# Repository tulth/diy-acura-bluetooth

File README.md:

# diy-acura-bluetooth
Overview
====================
My DIY project to understand, communicate, and add bluetooth with a 1999 Acura RL bose head unit

Cloning
====================
Be sure to include 

    --recursive 
  
during the git clone to get the submodules!

If you missed this, and do not want to reclone, do the following:

    git submodule update --init --recursive

Building
====================
Build platform:
Arch linux 
with community package: arm-none-eabi-gcc 5.3.0-1
with community package: arm-none-eabi-newlib
with package: python

Desktop shared library
------------
    cd target_desktop
    ./make.sh

Teensy3 embedded executables
------------
    cd target_teensy3
    ./make.sh

Loading
====================
To load you will need this arch linux AUR: teensy-loader-cli

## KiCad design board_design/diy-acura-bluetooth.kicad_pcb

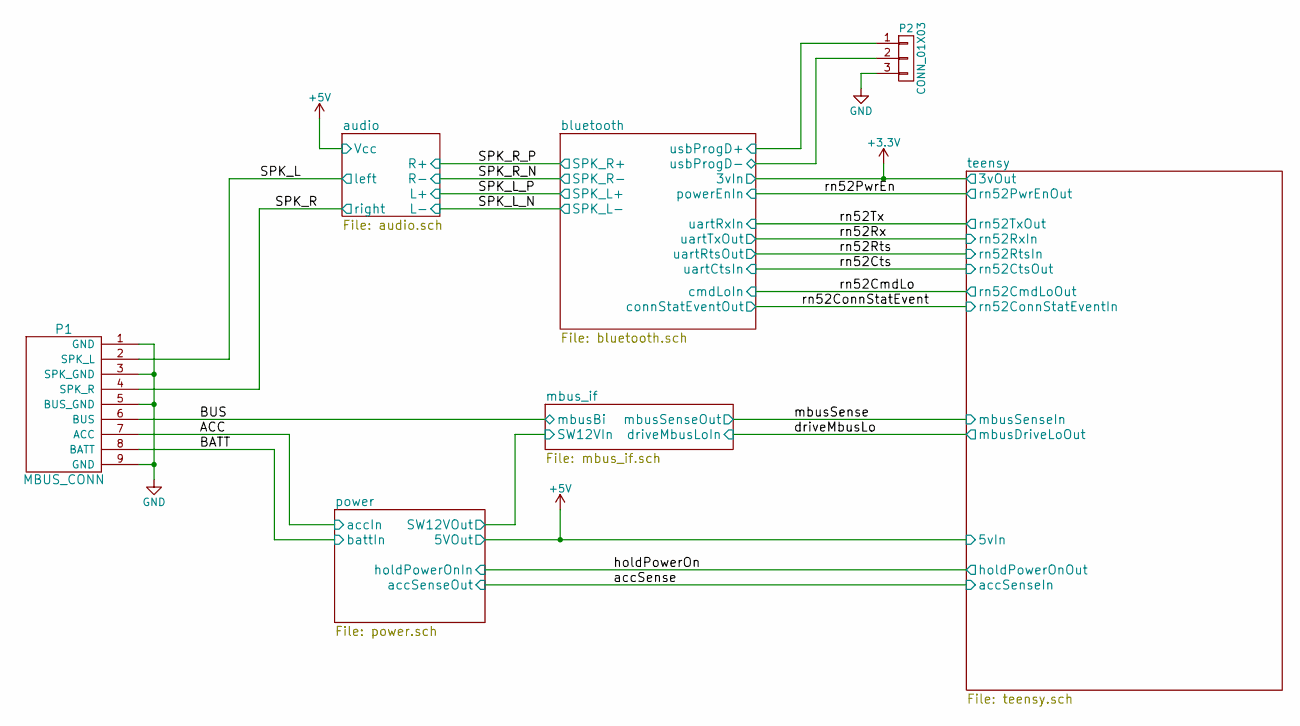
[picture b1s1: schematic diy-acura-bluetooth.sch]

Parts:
P1: MBUS_CONN; mbus_conn
P2: CONN_01X03; Pin_Header_Straight_1x03

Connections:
/audio/left: P1.2 (SPK_L); also elsewhere on the board
/audio/right: P1.4 (SPK_R); also elsewhere on the board
/bluetooth/usbProgD+: P2.1; also elsewhere on the board
/bluetooth/usbProgD-: P2.2; also elsewhere on the board
/mbus_if/mbusBi: P1.6 (BUS); also elsewhere on the board
/power/accIn: P1.7 (ACC); also elsewhere on the board
/power/battIn: P1.8 (BATT); also elsewhere on the board
GND: P1.1 (GND), P1.3 (SPK_GND), P1.5 (BUS_GND), P1.9 (GND), P2.3; also elsewhere on the board

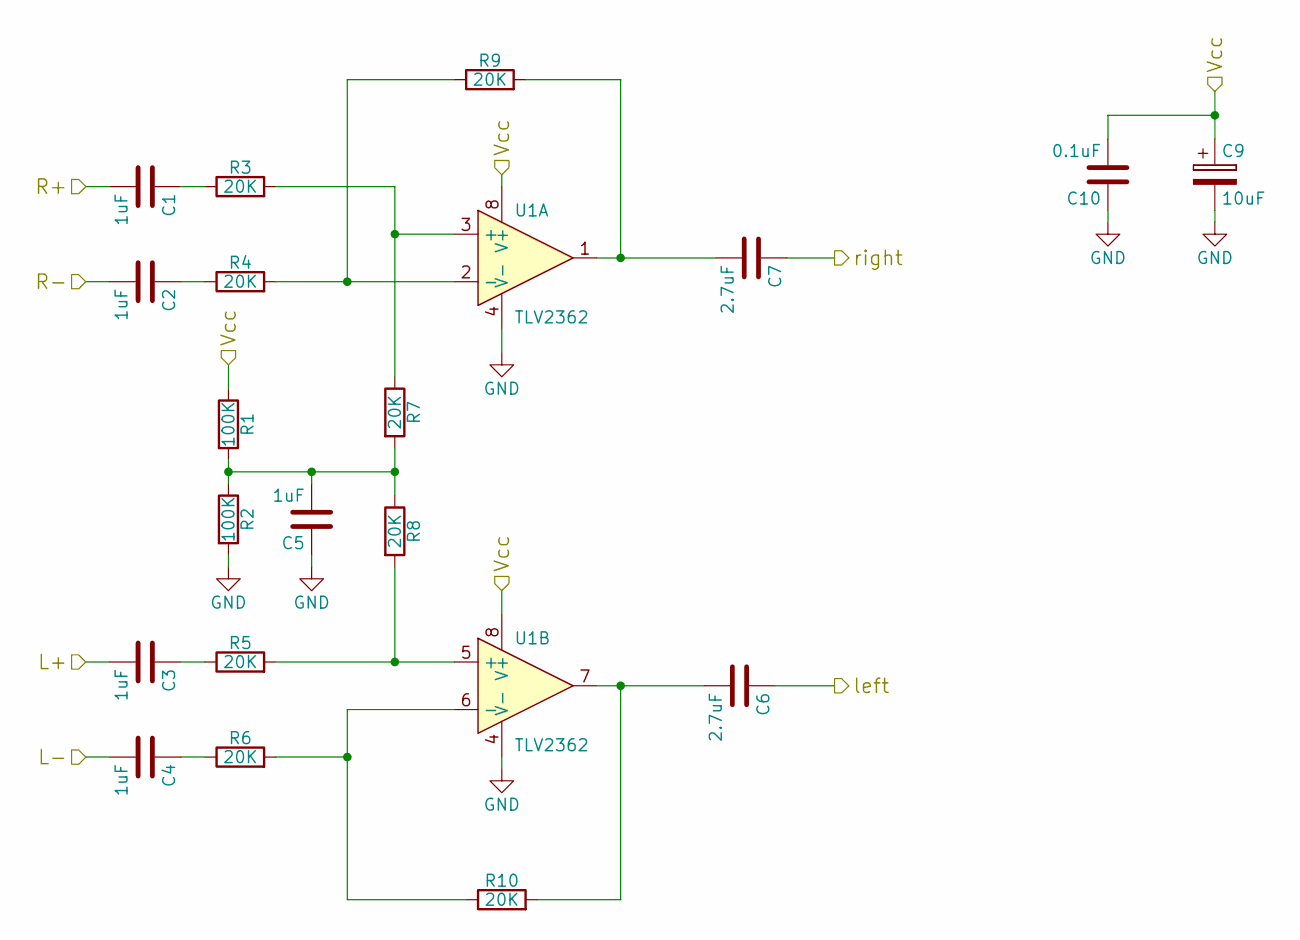
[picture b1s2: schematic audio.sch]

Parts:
C1, C2, C3, C4, C5: 1uF; C_Rect_L7.5_W6.5_P5
C6, C7: 2.7uF; C_Rect_L27_W9_H17_P23
C9: 10uF; C_Radial_D5_L11_P2
C10: 0.1uF; C_Disc_D6_P5
R1, R2: 100K; Resistor_Horizontal_RM10mm
R3, R4, R5, R6, R7, R8, R9, R10: 20K; Resistor_Horizontal_RM10mm
U1: TLV2362; DIP-8_W7.62mm_LongPads

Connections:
+5V: C9.1, C10.2, R1.1, U1.8 (V+); also elsewhere on the board
/audio/L+: C3.2; also elsewhere on the board
/audio/L-: C4.2; also elsewhere on the board
/audio/R+: C1.2; also elsewhere on the board
/audio/R-: C2.2; also elsewhere on the board
/audio/left: C6.1; also elsewhere on the board
/audio/right: C7.1; also elsewhere on the board
GND: C5.1, C9.2, C10.1, R2.2, U1.4 (V-); also elsewhere on the board
unnamed: C1.1, R3.1
unnamed: C2.1, R4.1
unnamed: C3.1, R5.1
unnamed: C4.1, R6.1
unnamed: C5.2, R1.2, R2.1, R7.2, R8.1
unnamed: C6.2, R10.2, U1.7
unnamed: C7.2, R9.2, U1.1
unnamed: R3.2, R7.1, U1.3 (+)
unnamed: R4.2, R9.1, U1.2 (-)
unnamed: R5.2, R8.2, U1.5 (+)
unnamed: R6.2, R10.1, U1.6 (-)

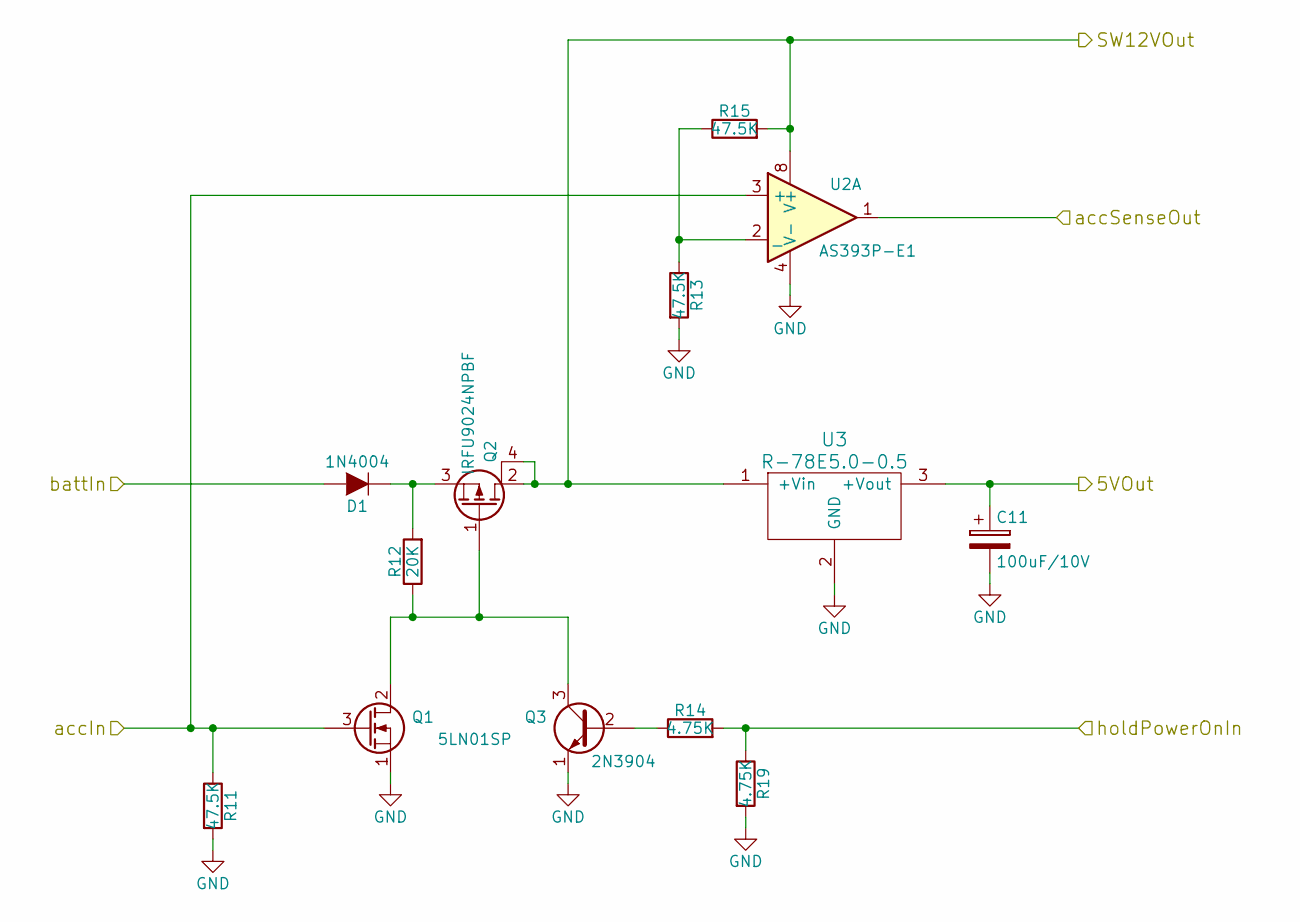
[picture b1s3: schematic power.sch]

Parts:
C11: 100uF/10V; C_Radial_D5_L11_P2
D1: 1N4004; Diode_DO-41_SOD81_Horizontal_RM10
Q1: 5LN01SP; TO-92_Molded_Wide_Oval
Q2: IRFU9024NPBF; TO-251AA-TPAD
Q3: 2N3904; TO-92_Molded_Wide_Oval
R11, R13, R15: 47.5K; Resistor_Horizontal_RM10mm
R12: 20K; Resistor_Horizontal_RM10mm
R14, R19: 4.75K; Resistor_Horizontal_RM10mm
U2: AS393P-E1; DIP-8_W7.62mm_LongPads
U3: R-78E5.0-0.5

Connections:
+5V: C11.1, U3.3 (+Vout); also elsewhere on the board
/mbus_if/SW12VIn: Q2.2 (D), Q2.4 (D), R15.2, U2.8 (V+), U3.1 (+Vin); also elsewhere on the board
/power/accIn: Q1.3 (G), R11.1, U2.3 (+); also elsewhere on the board
/power/battIn: D1.2 (A); also elsewhere on the board
/power/holdPowerOnIn: R14.2, R19.1; also elsewhere on the board
/teensy/accSenseIn: U2.1; also elsewhere on the board
GND: C11.2, Q1.1 (S), Q3.1 (E), R11.2, R13.2, R19.2, U2.4 (V-), U3.2 (GND); also elsewhere on the board
unnamed: D1.1 (K), Q2.3 (S), R12.2
unnamed: Q1.2 (D), Q2.1 (G), Q3.3 (C), R12.1
unnamed: Q3.2 (B), R14.1
unnamed: R13.1, R15.1, U2.2 (_)

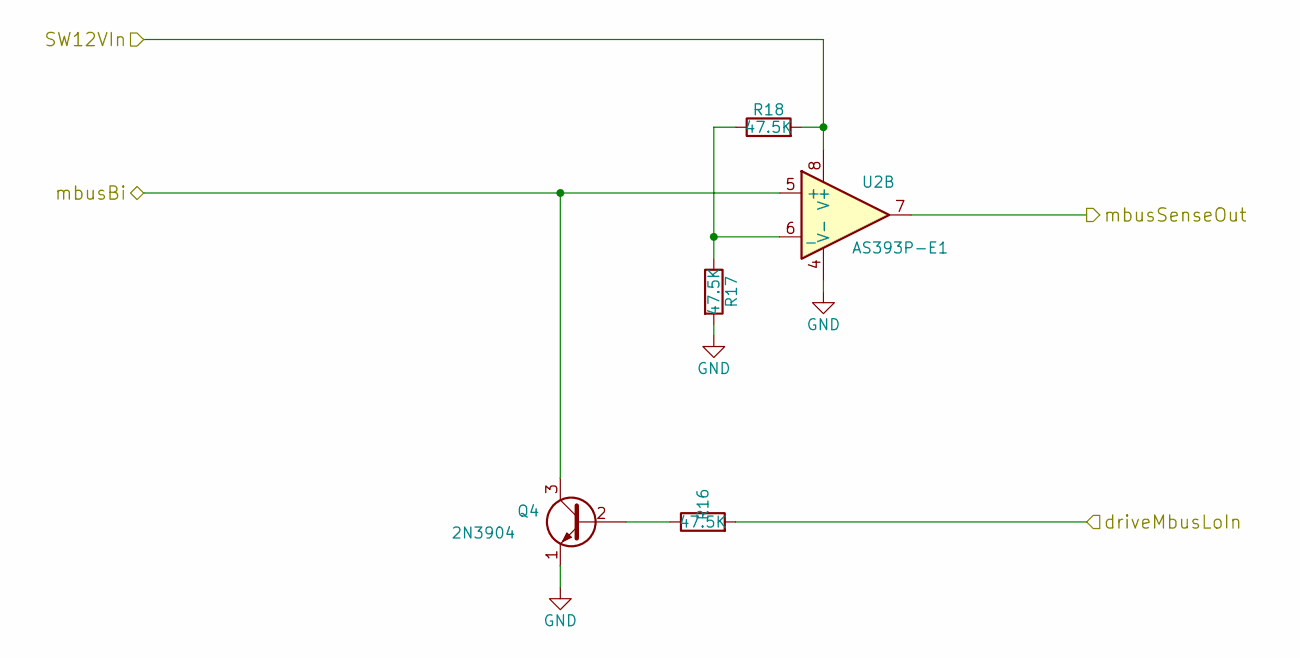
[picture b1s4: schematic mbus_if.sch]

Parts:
Q4: 2N3904; TO-92_Molded_Wide_Oval
R16, R17, R18: 47.5K; Resistor_Horizontal_RM10mm
U2: AS393P-E1; DIP-8_W7.62mm_LongPads

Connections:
/mbus_if/SW12VIn: R18.2, U2.8 (V+); also elsewhere on the board
/mbus_if/driveMbusLoIn: R16.2; also elsewhere on the board
/mbus_if/mbusBi: Q4.3 (C), U2.5 (+); also elsewhere on the board
/teensy/mbusSenseIn: U2.7; also elsewhere on the board
GND: Q4.1 (E), R17.2, U2.4 (V-); also elsewhere on the board
unnamed: Q4.2 (B), R16.1
unnamed: R17.1, R18.1, U2.6 (_)

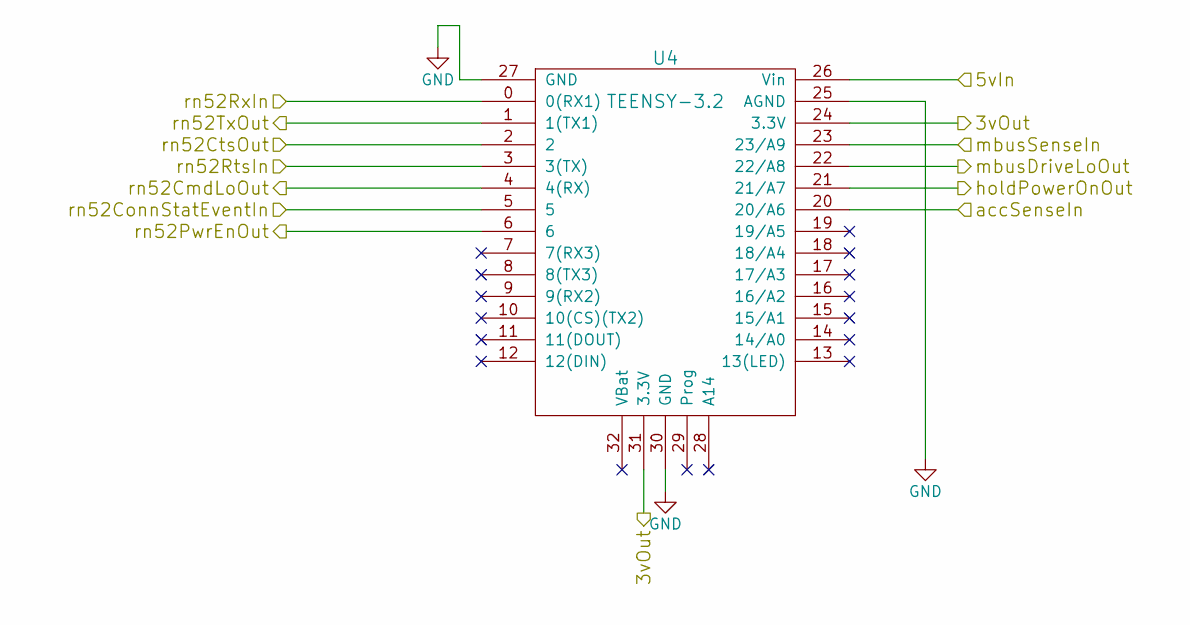
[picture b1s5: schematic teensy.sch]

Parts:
U4: TEENSY-3.2; Teensy-3.1

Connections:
+3V3: U4.24 (3.3V), U4.31 (3.3V); also elsewhere on the board
+5V: U4.26 (Vin); also elsewhere on the board
/bluetooth/cmdLoIn: U4.4 (4(RX)); also elsewhere on the board
/bluetooth/connStatEventOut: U4.5; also elsewhere on the board
/bluetooth/powerEnIn: U4.6; also elsewhere on the board
/mbus_if/driveMbusLoIn: U4.22 (22/A8); also elsewhere on the board
/power/holdPowerOnIn: U4.21 (21/A7); also elsewhere on the board
/teensy/accSenseIn: U4.20 (20/A6); also elsewhere on the board
/teensy/mbusSenseIn: U4.23 (23/A9); also elsewhere on the board
/teensy/rn52CtsOut: U4.2; also elsewhere on the board
/teensy/rn52RtsIn: U4.3 (3(TX)); also elsewhere on the board
/teensy/rn52RxIn: U4.0 (0(RX1)); also elsewhere on the board
/teensy/rn52TxOut: U4.1 (1(TX1)); also elsewhere on the board
GND: U4.25 (AGND), U4.27 (GND), U4.30 (GND); also elsewhere on the board

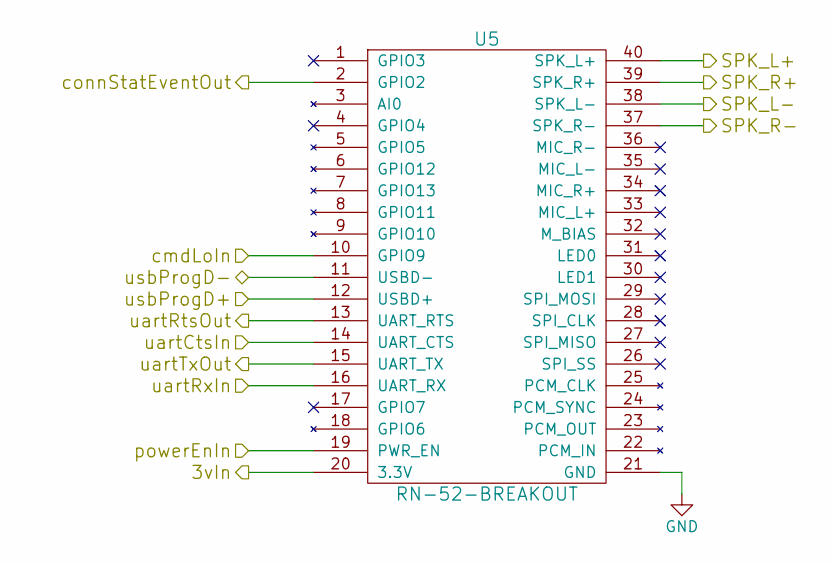
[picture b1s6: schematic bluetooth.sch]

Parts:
U5: RN-52-BREAKOUT

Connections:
+3V3: U5.20 (3.3V); also elsewhere on the board
/audio/L+: U5.40 (SPK_L+); also elsewhere on the board
/audio/L-: U5.38 (SPK_L-); also elsewhere on the board
/audio/R+: U5.39 (SPK_R+); also elsewhere on the board
/audio/R-: U5.37 (SPK_R-); also elsewhere on the board
/bluetooth/cmdLoIn: U5.10 (GPIO9); also elsewhere on the board
/bluetooth/connStatEventOut: U5.2 (GPIO2); also elsewhere on the board
/bluetooth/powerEnIn: U5.19 (PWR_EN); also elsewhere on the board
/bluetooth/usbProgD+: U5.12 (USBD+); also elsewhere on the board
/bluetooth/usbProgD-: U5.11 (USBD-); also elsewhere on the board
/teensy/rn52CtsOut: U5.14 (UART_CTS); also elsewhere on the board
/teensy/rn52RtsIn: U5.13 (UART_RTS); also elsewhere on the board
/teensy/rn52RxIn: U5.15 (UART_TX); also elsewhere on the board
/teensy/rn52TxOut: U5.16 (UART_RX); also elsewhere on the board
GND: U5.21 (GND); also elsewhere on the board

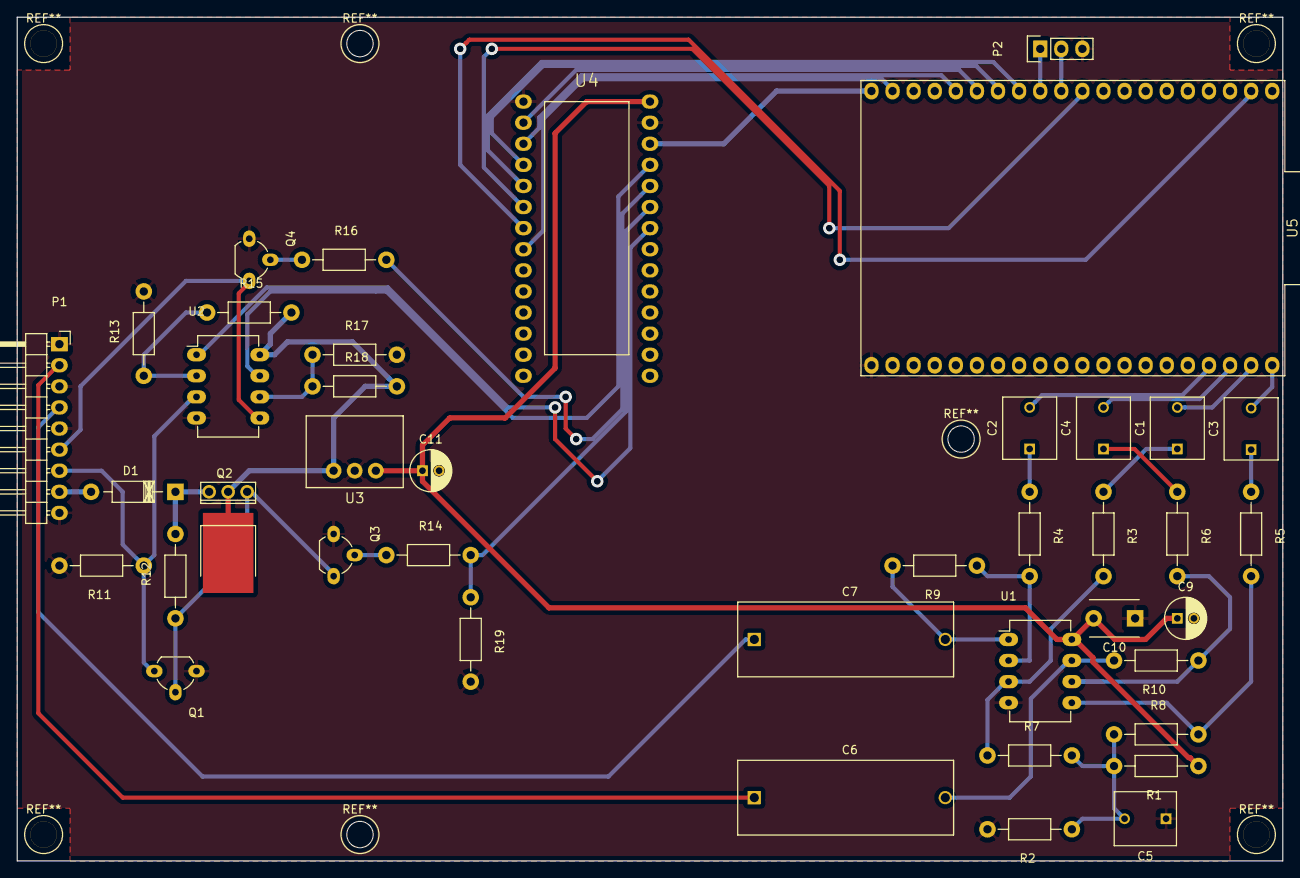
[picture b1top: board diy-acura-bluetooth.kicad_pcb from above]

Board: 2 copper layers, 152.4 x 101.6 mm, 41 parts (0 on the bottom side), 43 nets.

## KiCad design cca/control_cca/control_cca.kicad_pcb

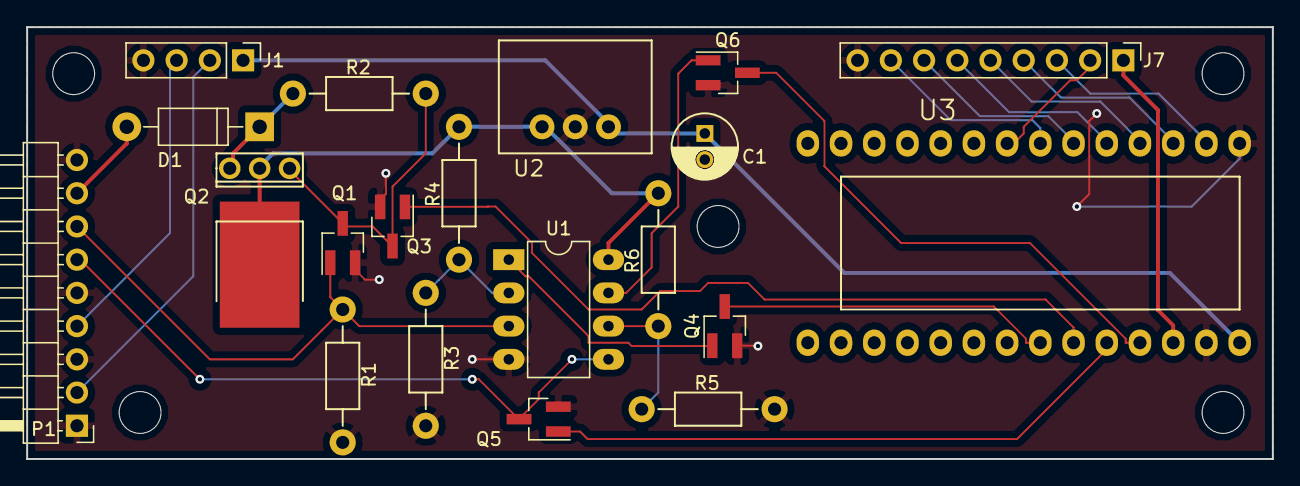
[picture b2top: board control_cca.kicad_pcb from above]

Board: 2 copper layers, 95.2 x 33.0 mm, 25 parts (0 on the bottom side), 26 nets.

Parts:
C1: ECA-1AM101; C_Radial_D5_L12_P2
D1: 1N4004; D_DO-41_SOD81_P10.16mm_Horizontal
J1: Conn_01x04; Pin_Header_Straight_1x04_Pitch2.54mm
J7: Conn_01x09; Pin_Header_Straight_1x09_Pitch2.54mm
MK1, MK2, MK3, MK4, MK5: Mounting_Hole; MountingHole_3.2mm_M3_ISO14580
P1: MBUS_CONN; Pin_Header_Angled_1x09_Pitch2.54mm
Q1, Q3, Q4, Q5, Q6: BSS138N; SOT-23_Handsoldering
Q2: IRFU9024NPBF; TO-251AA-TPAD
R1, R3, R4, R6: 47.5K; Resistor_Horizontal_RM10mm
R2, R5: 20K; Resistor_Horizontal_RM10mm
U1: AS393P-E1; DIP-8_W7.62mm_LongPads
U2: R-78E5.0-0.5
U3: TEENSY-LC; Teensy-3.2

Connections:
+3V3: J7.1, U3.24
+5V: C1.1, J1.1, U2.3, U3.26
/ACC: P1.7, Q1.1, R1.1, U1.3
/BATT: D1.2, P1.8
/BUS: P1.6, Q5.3, U1.5
/SPK_L: J1.2, P1.2
/SPK_R: J1.3, P1.4
/mbus_if/mbusDriveLowIn: Q5.1, U3.22
/power/holdPowerOnIn: Q3.1, U3.21
/power/protBattIn: D1.1, Q2.3, R2.1
/power/sw12VOut: Q2.2, Q2.4, R4.2, R6.2, U1.8, U2.1
/teensy/accLowIn: Q4.3, U3.20
/teensy/mbusSenseLowIn: Q6.3, U3.23
/teensy/rn52CmdLoOut: J7.7, U3.4
/teensy/rn52ConnStatEventIn: J7.8, U3.5
/teensy/rn52CtsOut: J7.5, U3.2
/teensy/rn52PwrEnOut: J7.2, U3.6
/teensy/rn52RtsIn: J7.6, U3.3
/teensy/rn52RxIn: J7.3, U3.0
/teensy/rn52TxOut: J7.4, U3.1
GND: C1.2, J1.4, J7.9, P1.1, P1.3, P1.5, P1.9, Q1.2, Q3.2, Q4.2, Q5.2, Q6.2, R1.2, R3.2, R5.2, U1.4, U2.2, U3.25, U3.27
unnamed: Q1.3, Q2.1, Q3.3, R2.2
unnamed: Q4.1, U1.1
unnamed: Q6.1, U1.7
unnamed: R3.1, R4.1, U1.2
unnamed: R5.1, R6.1, U1.6

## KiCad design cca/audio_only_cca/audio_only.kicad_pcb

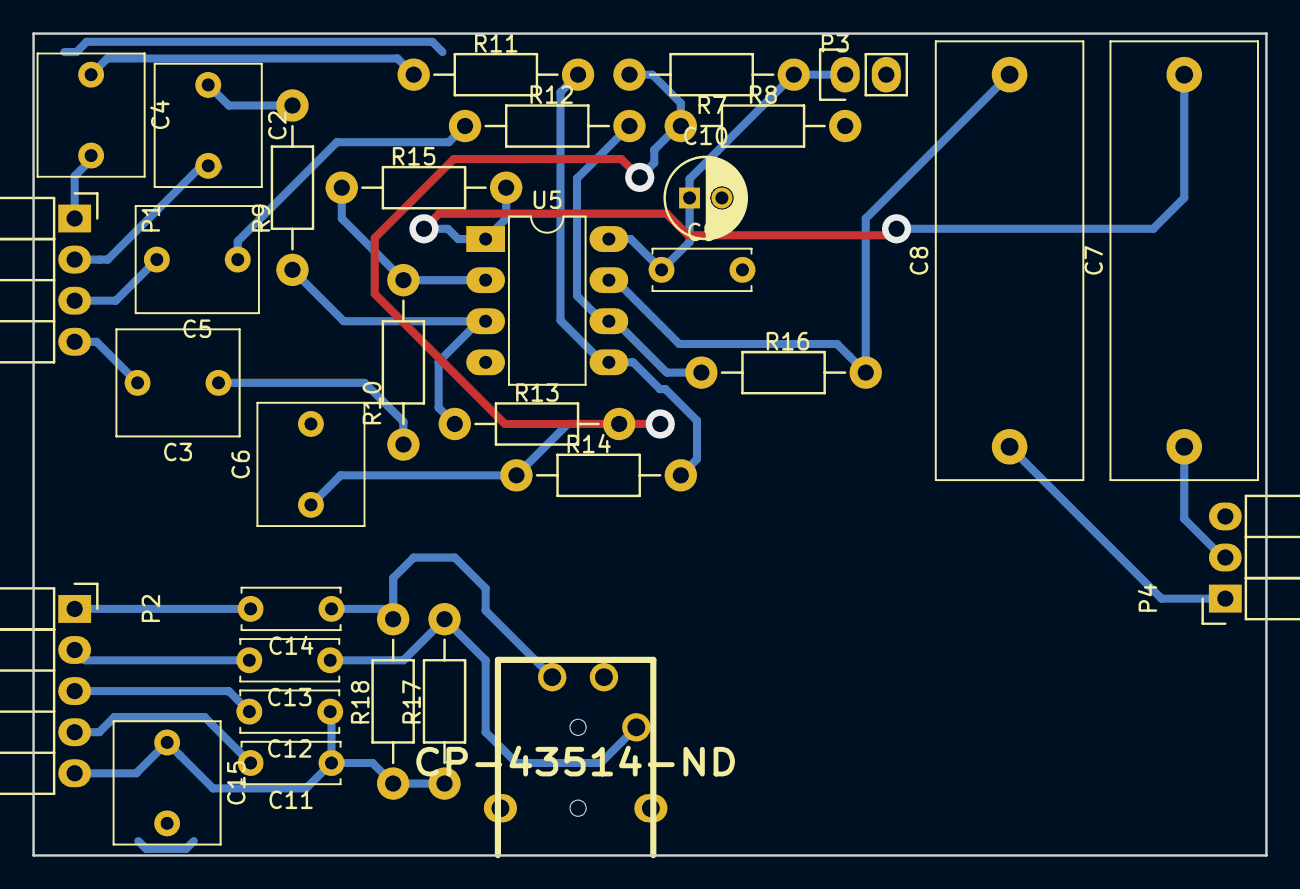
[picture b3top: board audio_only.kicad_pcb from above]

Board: 2 copper layers, 76.2 x 50.8 mm, 32 parts (0 on the bottom side), 26 nets.

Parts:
C2, C3, C4, C5, C6, C15: R82DC4100AA60K; C_Rect_L7.5mm_W6.5mm_P5.00mm
C7, C8: ECW-FD2W275K; C_Rect_L27.0mm_W9.0mm_P23.00mm
C9, C11, C12, C13, C14: K104K10X7RF5UH5; C_Disc_D6.0mm_W2.5mm_P5.00mm
C10: ECA-1AM101; C_Radial_D5_L12_P2
J1: CP-43514-ND; 4pin35mmAudio
P1: TCONN_01X04; Socket_Strip_Angled_1x04
P2: TCONN_01X05; Socket_Strip_Angled_1x05
P3: TCONN_01X02; Pin_Header_Straight_1x02
P4: TCONN_01X03; Socket_Strip_Angled_1x03
R7, R8: 100K; Resistor_Horizontal_RM10mm
R9, R10, R11, R12, R13, R14, R15, R16: 20K; Resistor_Horizontal_RM10mm
R17, R18: 2.2K; Resistor_Horizontal_RM10mm
U5: TLV2362; DIP-8_W7.62mm_LongPads

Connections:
/audio/MIC_L+: C11.2, P2.4
/audio/MIC_L-: C13.2, P2.2
/audio/MIC_R+: C12.2, P2.3
/audio/MIC_R-: C14.2, P2.1
/audio/M_BIAS: C11.1, C12.1, C15.1, P2.5, R17.1, R18.1
/audio/SPK_L+: C4.2, P1.1
/audio/SPK_L-: C5.2, P1.3
/audio/SPK_R+: C2.2, P1.2
/audio/SPK_R-: C3.2, P1.4
/audio/Vcc: C9.1, C10.1, P3.1, R7.1, U5.8
/audio/mic_left: C13.1, J1.2, R17.2
/audio/mic_right: C14.1, J1.3, R18.2
/audio/spk_left: C8.1, P4.1
/audio/spk_right: C7.1, P4.2
GND: C6.2, C9.2, C10.2, C15.2, J1.1, P3.2, P4.3, R8.2, U5.4
unnamed: C2.1, R9.1
unnamed: C3.1, R10.1
unnamed: C4.1, R11.1
unnamed: C5.1, R12.1
unnamed: C6.1, R7.2, R8.1, R13.2, R14.1
unnamed: C7.2, R15.2, U5.1
unnamed: C8.2, R16.2, U5.7
unnamed: R10.2, R15.1, U5.2
unnamed: R11.2, R14.2, U5.5
unnamed: R12.2, R16.1, U5.6
unnamed: R9.2, R13.1, U5.3

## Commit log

2016-02-23 Initial check-in of work that was formerly in a non-github repo.
2016-02-23 Now referencing the teensy3 core git repo as a submodule.
2016-02-23 Update toggles to use new mbus time format.
2016-02-23 move broken python py_lib develoment to dev branch, delete from master branch.
2016-02-23 Turn up the compile warning error reporting on internal code. Update teensy3 submodule code to not use these strict flags because it fails these.Turn up the compile warning error reporting on interna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
2016-02-23 add comment on arm newlib dependency
2016-02-23 teensy3 cmake: remove duplication by looping over top targets
2016-02-25 Add back py lib files to dev.
2016-02-25 Added back capability for python to simulate nibble-based messages pushed through mbus_phy (rx)
2016-02-25 Added nibble printing for MBUS error codes.
2016-02-25 Added toggle to phy rx
2016-02-26 reworking embedded exes to new naming plan
2016-02-27 Added embedded executables: bt_bridge (bluetooth), mbus_msg_sniffer, mbus_nibble_bridge, mbus_toggle_bridge. Reworked mbus_link to be its own layer with fifo's with hooks for TX capability (though TX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
2016-03-05 add nibbles to mbus link rx
2016-03-06 speedup: Update intervalized toggles to 10 intervals before the first toggle.
2016-03-06 fix: MBUS_END_MSG_CODE is now in nibbles
2016-03-06 add toggle captures
2016-03-06 fix: circ buf nonmalloc init should specify bufsize, not capacity
2016-03-06 separate nibble list from the nibble list ctypes struct.
2016-03-06 pep8 cleanup
2016-03-06 extra printing on nibble array struct
2016-03-06 cleanup
2016-03-06 toggles to phy then link capability
2016-03-06 add noshuttle bit field. fix python printing issue on pong msg.
2016-03-11 Add a single ping reply tester script
2016-03-11 Add helpful teensy programmer script
2016-03-11 Add mbus_phy_tx_is_empty
2016-03-11 fix: mbus tx switches back to rx before the last tx nibble is finished
2016-03-11 fix: incorrect bufsize for link msg bufs. fix: nibble sniffer did not enable rx.
2016-03-11 add commented out mbus drive pin capability
2016-03-13 fix: mbus rx always busy bug
2016-03-13 fix port setup assignment to not use |=. init driveMbusPinLo as false. Drive portc1 high when driveMbusPinLo is 1.
2016-03-13 toggle bridge: drive low when input is character 0, not integer 0
2016-03-13 mbus tx: placeholders for bit-packed nibble structs
2016-03-13 mbus rx: Renaming pass for nibbles and msg
2016-03-13 Update link module with prelim tx capability and rx/tx direction control
2016-03-13 Partial bt bridge rewrite to be more like other executables
2016-03-13 Renamed circular_buffer to fifo. updated python scripts to have/use MbusTxMsgStruct. Fixed python MbusRawNibbleListStructList to use MbusRawNibbleListList
2016-03-13 Cleanup pass: make all teensy main progs consistent.
2016-03-14 Added rn52, new app_demo to try in the garage.
2016-03-15 garage fixes: always busy tx phy bug, link:bad packed tx transmission and do not send pending tx the queue is empty. Disable rn 52 section for now.
2016-03-16 new debug printing. RN52 enabled and prints state changes.
2016-03-16 rn52 debug
2016-03-18 mbus phy: Added transmit turnaround time.
2016-03-18 app demo toggle sniffer main, debug print defaults to no newline now, added defines to enable module level debugging, more debugging code
2016-03-18 fix rx->tx checksum bug: caused by rx enable resetting rx back to idle mode
2016-03-20 many fixes. now music plays and next/previous work. added fifo id for fifo debug
2016-03-29 adding the work in progress board design to git
2017-01-21 WIP commit before redoing layout for 0.5mm bit and before adding microphone port.
2017-01-22 Add kicad common
2017-01-22 Add kicad cca folder gitignore
2017-01-22 Add:Audio only cca. Plan:test opamp design
2017-01-22 Pull in Kicad common updates.
2017-01-22 Add generated netlist to git ignore
2017-01-22 Add/use custom headers because orign drill sizes were 1.0016mm
2017-01-22 fix: footprint for 1x5 connector
2017-01-28 Built and fabbed the audio board. It mostly works except for audio on/off changes causes popping only on the right channel.
2017-01-28 further garage debugging
2017-02-05 Garage code updates
2018-03-04 control cca sent to osh park
2018-03-29 add build for teensy lc
2018-03-30 teensy3 is slightly different than teensy lc pins start using core pins bitmask
2018-03-30 start a bt toggle sniffer for debug, not yet finished
2018-03-30 teensy3 is slightly different than teensy lc pins pt 2 start using core pins bitmask
2018-03-30 add test cts drive for debug
2018-03-30 switch all pin pits to use core pins
2018-03-30 attempt cmd lo pin fix on app_demo and bt bridge
2018-03-31 reconnect bt on power on and no rn52 debug, mostly works sometimes the head unit still fails to connect sometime the bt seems to be disabled
2018-03-31 rn52 reboot at start, can hang at start and manual restart fixed
2018-03-31 make bluetooth reconnect if not connected
2018-03-31 now that we reboot and connect to last, remove connect boot extfeat it could connect before reboot and confuse phone
2018-03-31 handle rn52 reboot cmd has a special reply
2018-03-31 fix handle rn52 reboot cmd has a special reply
2018-06-02 Add programmable reconnect
2019-05-24 add rn52 debug print on timeout
2019-05-24 add reboot on switch disk4
2019-06-09 change reboot to just reboot rn52. reboot teensy did not seem to work
2019-06-10 try sending reconnect last command 10 times for each console press
2020-03-08 add discovery(pairing), corrected pause did this before!
